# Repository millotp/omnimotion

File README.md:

# Omnimotion

A reusable three-axis motion controller — one board and one firmware stack —
shared across a family of home projects instead of building a bespoke controller
for each one.

<sub>Rev A.1, 98 × 99 mm, four layers. Rendered from the KiCad file with
[`render_pcb.py`](hardware/scripts/render_pcb.py); a few 3D models are stand-ins,
so connector shapes are approximate. A [top view](hardware/generated/omnimotion_pcb_top.jpg)
is alongside it.</sub>

## Why

A self-playing chessboard, a zen garden and a line-art drawing machine look
nothing alike, but underneath they all want the same thing: a few stepper axes
that move accurately, know where they are, and stop when something is wrong.
Rebuilding that from scratch every time buried the interesting part of each
project under motor drivers and homing routines.

Omnimotion is that common denominator, factored out once. Standing up a new
machine should be a matter of describing its geometry, not porting a driver.

## The two halves

| Folder | What it is |
| --- | --- |
| [`hardware/`](hardware/README.md) | The board — schematic, bill of materials, and the engineering rationale behind them. Both deliverables are generated from a script, so the drawing and the parts list cannot drift apart. |
| [`software/`](software/README.md) | The firmware — motion planning, step generation, stepper-driver control, homing, fault handling, and the board API that ties them together. |

Each folder has its own README with the specifics; this page is only the map.

Concretely, the board is an ESP32-S3 driving three TMC2209 stepper drivers, with
endstops, a two-pole emergency stop, a pair of switched outputs and a small
amount of general-purpose I/O. The firmware gives you one entry point that brings
that board up, works out what is actually fitted, and hands back something you
can command.

## What it optimises for

In priority order, because these trade against each other.

1. **Fail in the safe direction.** The motor drivers stay disabled unless
   firmware and the emergency-stop loop both agree they should be on, and that
   agreement is wired in copper rather than decided in software.
2. **Buildable by one person.** Every part is hand-solderable and orderable from
   a single distributor, and the parts list is short enough to read in full.
3. **Testable without hardware.** The motion logic is kept separate from
   anything chip-specific, so it can be unit-tested on a laptop.
4. **Modular.** Drivers, sensors and displays are all optional. The firmware
   surveys what is present at startup instead of assuming a fixed machine.

## Status

The schematic, bill of materials and PCB layout are complete and consistent with
each other, and the board is fully routed. The firmware builds with runnable
examples, and the motion core is covered by host tests. But **no board has been
fabricated yet**, so none of this has been validated against copper or a running
motor. Expect Rev A.1 to need a respin.

## Scope

This is hobby equipment. The emergency stop cuts motor torque in hardware, which
is a real and deliberate design choice — but it is not a certified safety
function, it does not de-energise the output rail, and it does not brake a loaded
axis. Anything that can injure someone or destroy itself needs protection that
does not depend on this board. Both folder READMEs are explicit about where the
limits sit.

## License

The firmware in `software/` is dual-licensed under either of
[Apache License 2.0](LICENSE-APACHE) or [MIT](LICENSE-MIT), at your option.

The hardware design in `hardware/` (schematic, PCB, bill of materials and the
scripts that generate them) is licensed under the
[CERN Open Hardware Licence Version 2 – Permissive](hardware/LICENSE)
(CERN-OHL-P-2.0).

Both are provided as is, with no warranty. Building and running a board that
switches motor power is entirely at your own risk.

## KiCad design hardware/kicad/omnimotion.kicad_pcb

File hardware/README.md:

# Omnimotion hardware

Rev A.1 of the Omnimotion board: a three-axis stepper motion controller built
around an ESP32-S3 module and three TMC2209 drivers.

One board is meant to serve every project in the family, so the I/O is
deliberately generic rather than tuned to any single machine — three axes, six
endstops, two switched output channels, an analogue input, and a pair of I²C
headers for whatever a given build needs.

Simplicity is a hard design constraint here rather than an afterthought: five
IC part numbers, one FET part number, one Schottky part number, and nothing on the board
that one person cannot hand-solder and reason about without a block diagram.
[`DESIGN_NOTES.md`](DESIGN_NOTES.md) keeps the honest accounting of what that
constraint costs.

## Specifications

| | |
| --- | --- |
| MCU | ESP32-S3-WROOM-1-N16R8 — dual core, 16 MB flash, 8 MB octal PSRAM, Wi-Fi/BLE, native USB |
| Axes | 3 × TMC2209-LA-T on a shared single-wire UART bus, with StallGuard4 for sensorless homing |
| Motor current | ≤ 1.4 A RMS per axis continuous, set in firmware over UART, on 0.11 Ω 2512 shunts |
| Input | 12–24 V DC via barrel jack or screw terminal, behind a 6.3 A replaceable fuse and a TVS clamp |
| 5 V rail | 3 A buck off the motor rail, multiplexed against USB with the buck as priority; 2.5 A usable |
| 3.3 V rail | Linear regulator, ~0.5 A usable |
| Endstops | 6 direct-GPIO inputs, dry contact or 3.3 V hall sensor, with polarity and role set per connector |
| Emergency stop | 2-pole normally-closed: one pole reports to firmware, the other sits in the driver-enable return |
| Outputs | 2 discrete low-side switches, 1 A each — one on 5 V, one on the 12–24 V rail |
| Other I/O | Analogue input, I²C OLED header, I²C expansion header, addressable RGB pixel, aux power take-off |
| PCB | 4 layers, 1.6 mm FR-4, ENIG |
| Assembly | 0603 minimum, 48 BOM lines covering 174 placed parts and 15 bare test pads, sized for one stencil and a hot plate |

Fifteen test points cover every rail and every bus worth scoping. Two GPIOs are
spare, and both are strapping pins, so in practice the module is full.

## Connectors

| Ref | Part / pitch | Function |
| --- | --- | --- |
| J1 | DC-005 barrel, 5.5/2.1 mm | 12–24 V DC input |
| J2 | 2-pin screw, 2.54 mm | 12–24 V DC input, high current |
| J3 | 4-pin screw, 2.54 mm | 2-pole NC emergency stop: sense + enable return |
| J4 | USB-C 2.0 | USB data and 5 V |
| J5 | 4-pin header, 2.54 mm | Console / spare UART |
| J6 | 4-pin header, 2.54 mm | I²C OLED |
| J7 | 4-pin header, 2.54 mm | I²C expansion |
| J8–J10 | 4-pin header, 2.54 mm | Stepper motors M0–M2 |
| J11–J16 | 3-pin header, 2.54 mm | Endstops, min and max per axis |
| J17 | 3-pin header, 2.54 mm | Analogue input |
| J18 | 2-pin screw, 2.54 mm | OUT1, 5 V low-side |
| J19 | 2-pin screw, 2.54 mm | OUT2, 12–24 V low-side |
| J20 | 3-pin screw, 2.54 mm | Addressable RGB strip |
| J21 | 4-pin screw, 2.54 mm | Aux power take-off |
| SW1 / SW2 | 3 × 6 mm tactile | Reset, and the boot strap for flashing |

## What is in this folder

| Path | Contents |
| --- | --- |
| `generated/omnimotion_schematic.svg` | The schematic, 9 sheets |
| `generated/omnimotion_pcb_{top,angle}.jpg` | 3D renders of the PCB, made by `scripts/render_pcb.py` |
| `generated/omnimotion_BOM.csv` | Bill of materials as one table: a row per part, with manufacturer and Digi-Key part numbers, the KiCad footprint it needs, the sheets it appears on, and the datasheet rating that justifies it |
| `generated/omnimotion_footprints.html` | Printable parts list plus every distinct footprint the BOM needs drawn at 1:1, to lay the real parts on before the PCB is ordered. The generator also writes a PDF of it when Chrome is installed; that copy is not committed |
| `scripts/gen_schematic.py` | Generator for the schematic, and the source of truth for the design |
| `scripts/gen_bom.py` | Harvests the BOM out of the generator |
| `scripts/gen_footprint_sheet.py` | Builds the footprint sheet from the BOM and the footprints placed on the KiCad PCB |
| `scripts/render_pcb.py` | Renders the KiCad PCB to JPEG, or exports it as a STEP and GLB 3D model to paths you give, through Docker, no local KiCad needed |
| `scripts/check_kicad.py` | Compares the KiCad schematic with the generator, net by net, and the KiCad PCB with that schematic |
| `scripts/kicadlib.py` | Read-only KiCad file parsing (s-expressions, schematic connectivity, PCB pads) shared by the two scripts above |
| `scripts/schlib.py` | Minimal SVG primitive and symbol library the generator draws with |
| `DESIGN_NOTES.md` | Design rationale, datasheet verification, layout constraints, known risks |
| `kicad/` | KiCad 10 project `omnimotion`: the schematic, and the routed 4-layer PCB, 98 × 99 mm. Both follow the generated design and are checked against it by `check_kicad.py` |
| `LICENSE` | CERN-OHL-P-2.0, covering everything in this folder |

The sheets are ordered so you can read them front to back: 1 is the architecture
and power tree, 2 and 3 are input protection and the supplies, 4 is the MCU, 5–7
are one axis each, 8 is the endstops and the I²C headers, and 9 is the outputs,
test points and bring-up order. `DESIGN_NOTES.md` has the full index.

## Regenerating the deliverables

```bash
cd hardware
python3 scripts/gen_schematic.py && python3 scripts/gen_bom.py
```

No dependencies beyond a Python 3 interpreter; the generator writes SVG directly.
Add `--check` to either script to regenerate in memory and fail if the committed
file is stale.

Edit the generator, never the SVG or the CSV. Both scripts refuse to run on an
ambiguous drawing: a component terminal or wire end that touches nothing, a wire
drawn through another symbol, or a T-junction without a dot. `gen_bom.py` reads
its component list back out of the schematic generator and fails loudly on a
duplicate reference designator or a value with no BOM entry, which is what keeps
the two from disagreeing.

`python3 scripts/check_kicad.py` checks the `kicad/` project against the generator
without needing KiCad installed. It reports parts that are missing or extra,
values that differ, pins on the wrong net, design nets that KiCad shorts
together, and any part, footprint or pad net where the PCB has drifted from the
KiCad schematic. It also holds every footprint to the one the BOM names. It
exits non-zero when anything differs.

`python3 scripts/gen_footprint_sheet.py` rebuilds the footprint sheet after a BOM or PCB
change. It draws the footprint each BOM line names: from the PCB's own copy
when the PCB has it, compared pad by pad with the library (the project's
`.pretty` folder or the KiCad library downloaded into
`build/footprints/`), and from the library otherwise. References that are
missing from the PCB, or that sit on another footprint there, are flagged in
red. Capacitors show their voltage and dielectric. It prints the PDF with Google
Chrome when it is installed.

## Rendering the PCB

```bash
python3 scripts/render_pcb.py images
python3 scripts/render_pcb.py models board.step board.glb
```

`images` rewrites the two `generated/omnimotion_pcb_*.jpg` images from
`kicad/omnimotion.kicad_pcb`. `models` exports the same board as a 3D model and
needs a path for both the STEP and the GLB file. It has no default location,
because the files are several megabytes and are not kept in the repository. The
models take well under a minute, the renders a couple of minutes. The only
requirement is Docker, so KiCad does not have to be installed. The script:

1. Reads the 3D model paths out of the PCB and downloads each one, once, from
   the [official KiCad 3D library](https://gitlab.com/kicad/libraries/kicad-packages3D)
   into `build/3dmodels/` (git-ignored). The `kicad/kicad` image ships without
   3D models, which is why this step exists.
2. Pulls the `kicad/kicad:10.0` image if it is missing, and runs
   `kicad-cli pcb render` in it with the model folder mounted, once each for
   a top view and an angled perspective view.
3. Exports the board as a coloured 3D model with `kicad-cli pcb export step` and
   `export glb`: the board body, the component models and the soldermask, without
   copper pads, tracks, zones or silkscreen (the pads alone are 60% of the
   triangles). The STEP (6.8 MB) keeps solids and colours for CAD; the GLB (3.7 MB,
   about 95,000 triangles) carries PBR materials for viewers. Both are far
   heavier than a real-time scene should draw, so a consumer that animates the
   board in a browser should decimate them.
4. Copies the outputs out with `docker cp`, because a bind-mounted output folder
   is not reliably writable by the container's user. Each run names its container
   after its process id, so two runs at once do not stop each other.

The image is published for amd64 only. On Apple Silicon it runs under emulation,
and the two views take about a minute and a half together; after the first run the
models and the image are cached.

Four parts have no exact model in the KiCad library. The PCB points the Kycon
barrel jack (J1), the TMC2209 VQFN-28 (U5–U7) and the LMR33630 HTSOP-8 (U1) at
the closest library models, so their 3D shapes are approximate (the QFN model has
a 3.35 mm exposed pad against the footprint's 3.7 mm). The Littelfuse Nano2 fuse
holder (F1) has no model at all and is drawn as bare pads. Adjust the angle, zoom
or size in `VIEWS` at the top of the script.

## Building one

1. **Order.** Every orderable line carries a manufacturer part number and a
   Digi-Key link, so the board goes into a single cart. The four lines that do
   not are the PCB itself, the bare test pads, the mounting hardware and the
   optional driver heatsinks.
2. **Assemble.** Nothing is smaller than 0603 and there is exactly one FET part
   number and one Schottky part number on the board. Screw terminals, the USB-C
   hold-down and the 2.54 mm headers stay through-board on purpose: a yanked
   motor or endstop cable will lift an SMD pad. The ten signal headers snap
   off a single 40-pin breakaway strip; the motor headers are unkeyed, so mark
   pin 1 and never hot-plug a motor.
3. **Bring up in the printed order.** Sheet 9 lists it step by step — rails
   before ICs, the MCU before any driver, one driver before three. TP1–TP4 are
   the rail-by-rail power check and are worth doing before an IC goes on.
4. **Before ordering the PCB**, confirm the buck inductor footprint against the
   part you actually bought, and run DRC with your fab's real constraints.

## Limits worth knowing before you build

The full list is in [`DESIGN_NOTES.md`](DESIGN_NOTES.md); these are the ones that
change what you can safely do with the board.

- **Nothing here has been fabricated.** No claim in this folder has been checked
  against a physical board.
- **No overvoltage protection on the motor rail.** This is the headline risk.
  The TVS does not contain a large enough transient before the drivers' absolute
  maximum is exceeded; regeneration can do the same. Supply choice is the
  protection: a bench supply or a good brick on a short lead, not a long
  inductive feed or a supply shared with contactors.
- **The emergency stop cuts torque, not power.** Opening it releases the drivers
  in copper with no firmware involvement, which is the point — but the motor rail
  and the 24 V output stay live, and the motors coast rather than brake. A loaded
  vertical axis will back-drive. If something must drop mechanically, use a
  3-pole button or an external contactor.
- **Reverse polarity blows the fuse** rather than being blocked. The fuse is a
  replaceable cartridge, so the cost is a fuse — but feed the board 12–24 V and
  nothing else.
- **1.4 A RMS per axis is contingent on thermals.** The driver exposed pads are
  the entire heatsink; the thermal vias and the solid inner ground plane are not
  optional, and above ~1.2 A RMS per axis you want the adhesive heatsinks listed
  at the end of the BOM.
- **USB-only power is a 500 mA budget** enforced by a thermal PTC, not a precise
  limiter. No motors, no output loads.
- **The external inputs have no clamp diodes.** A 1 kΩ series resistor and a
  100 nF cap on each endstop and on J17 cover ESD, but nothing clamps a
  sustained wrong voltage. 24 V into a SIG pin will cost you a GPIO on a
  soldered-down module.

## Going deeper

[`DESIGN_NOTES.md`](DESIGN_NOTES.md) is the engineering record: which datasheet
was consulted for what and where one changed the plan, the emergency-stop
architecture in full, the power budget rail by rail, the pin map the firmware
depends on, the part vocabulary for home assembly, KiCad stackup and routing
constraints, and the open risks.

The firmware that drives this board is in [`../software/`](../software/README.md).

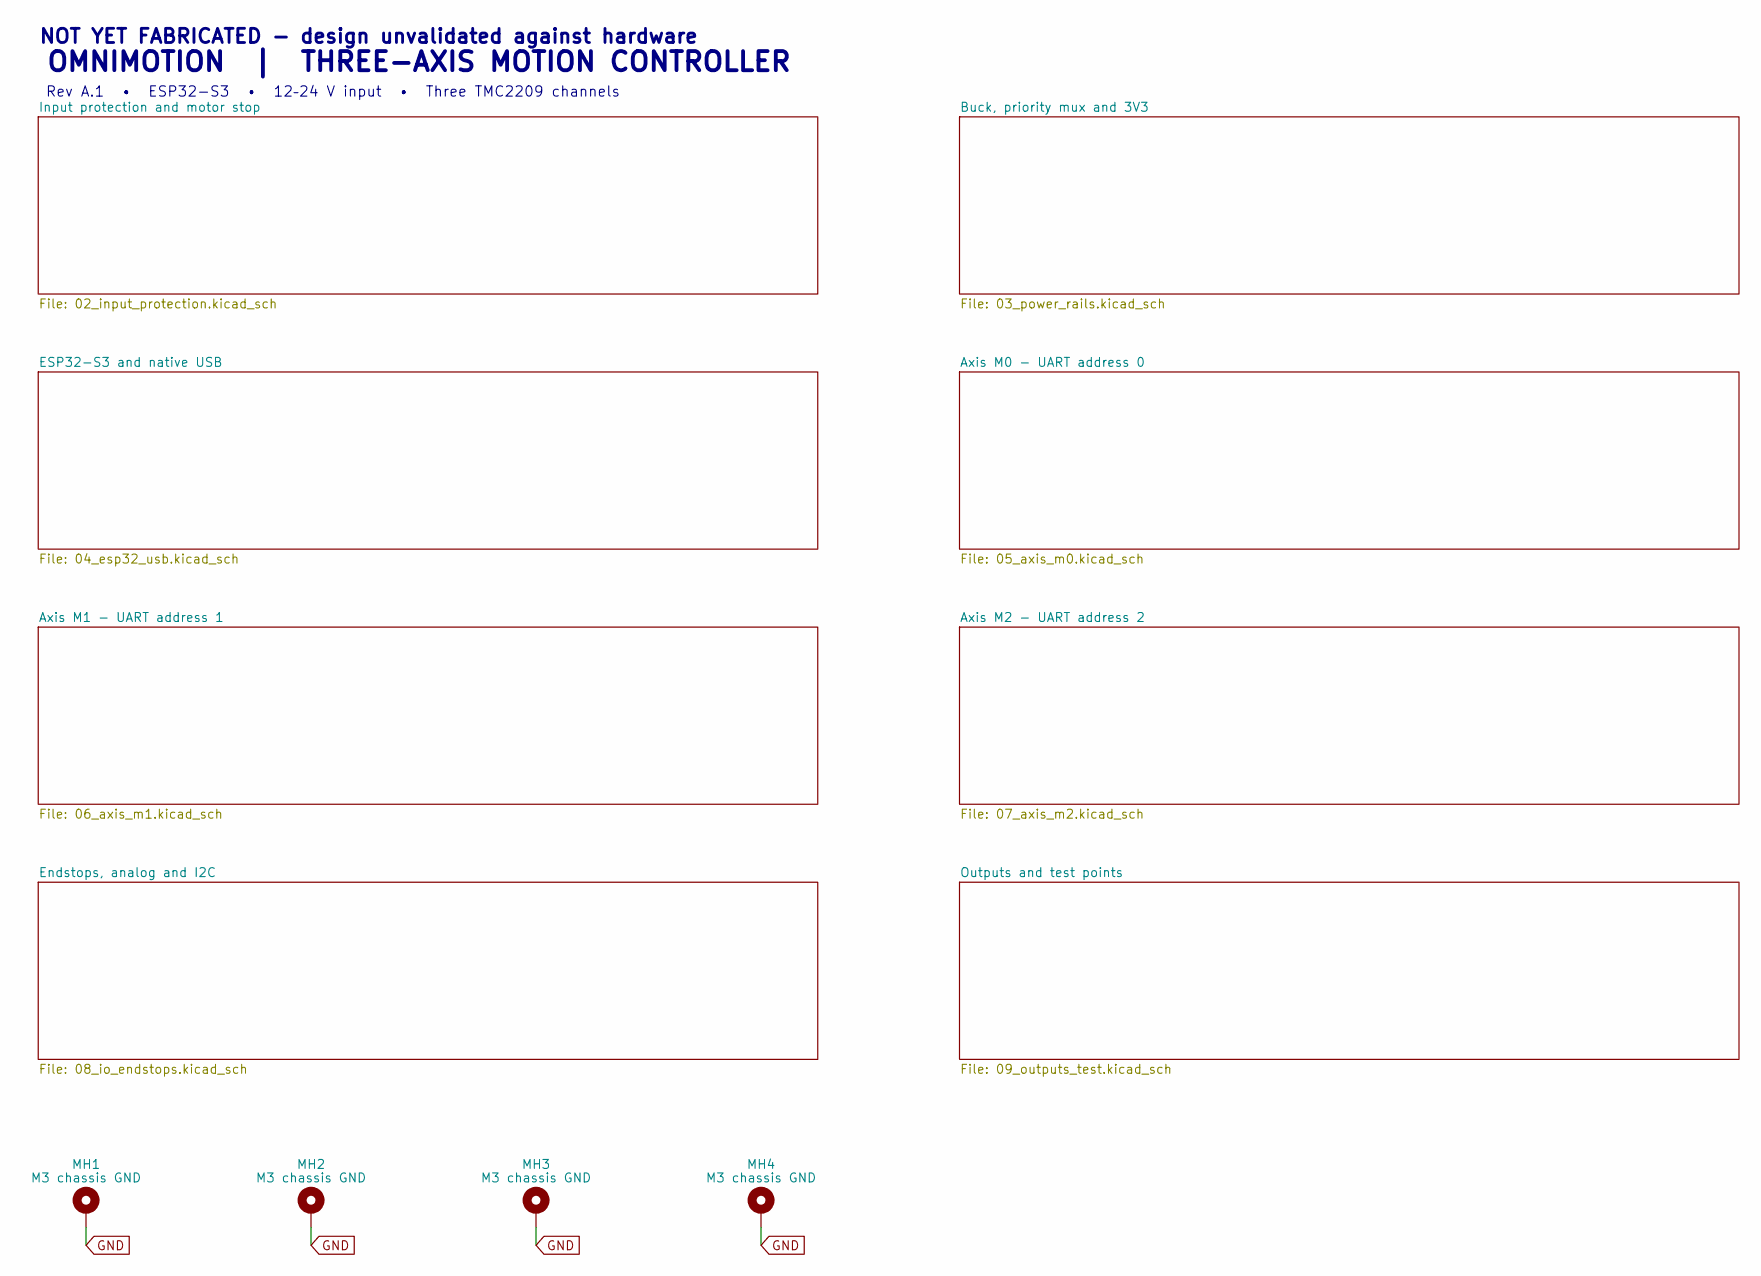
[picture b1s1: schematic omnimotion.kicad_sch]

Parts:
MH1, MH2, MH3, MH4: M3 chassis GND; MountingHole_3.2mm_M3_ISO7380_Pad

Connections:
GND: MH1.1 (1_1), MH2.1 (1_1), MH3.1 (1_1), MH4.1 (1_1); also elsewhere on the board

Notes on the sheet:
NOT YET FABRICATED - design unvalidated against hardware
OMNIMOTION | THREE-AXIS MOTION CONTROLLER
Rev A.1 • ESP32-S3 • 12–24 V input • Three TMC2209 channels

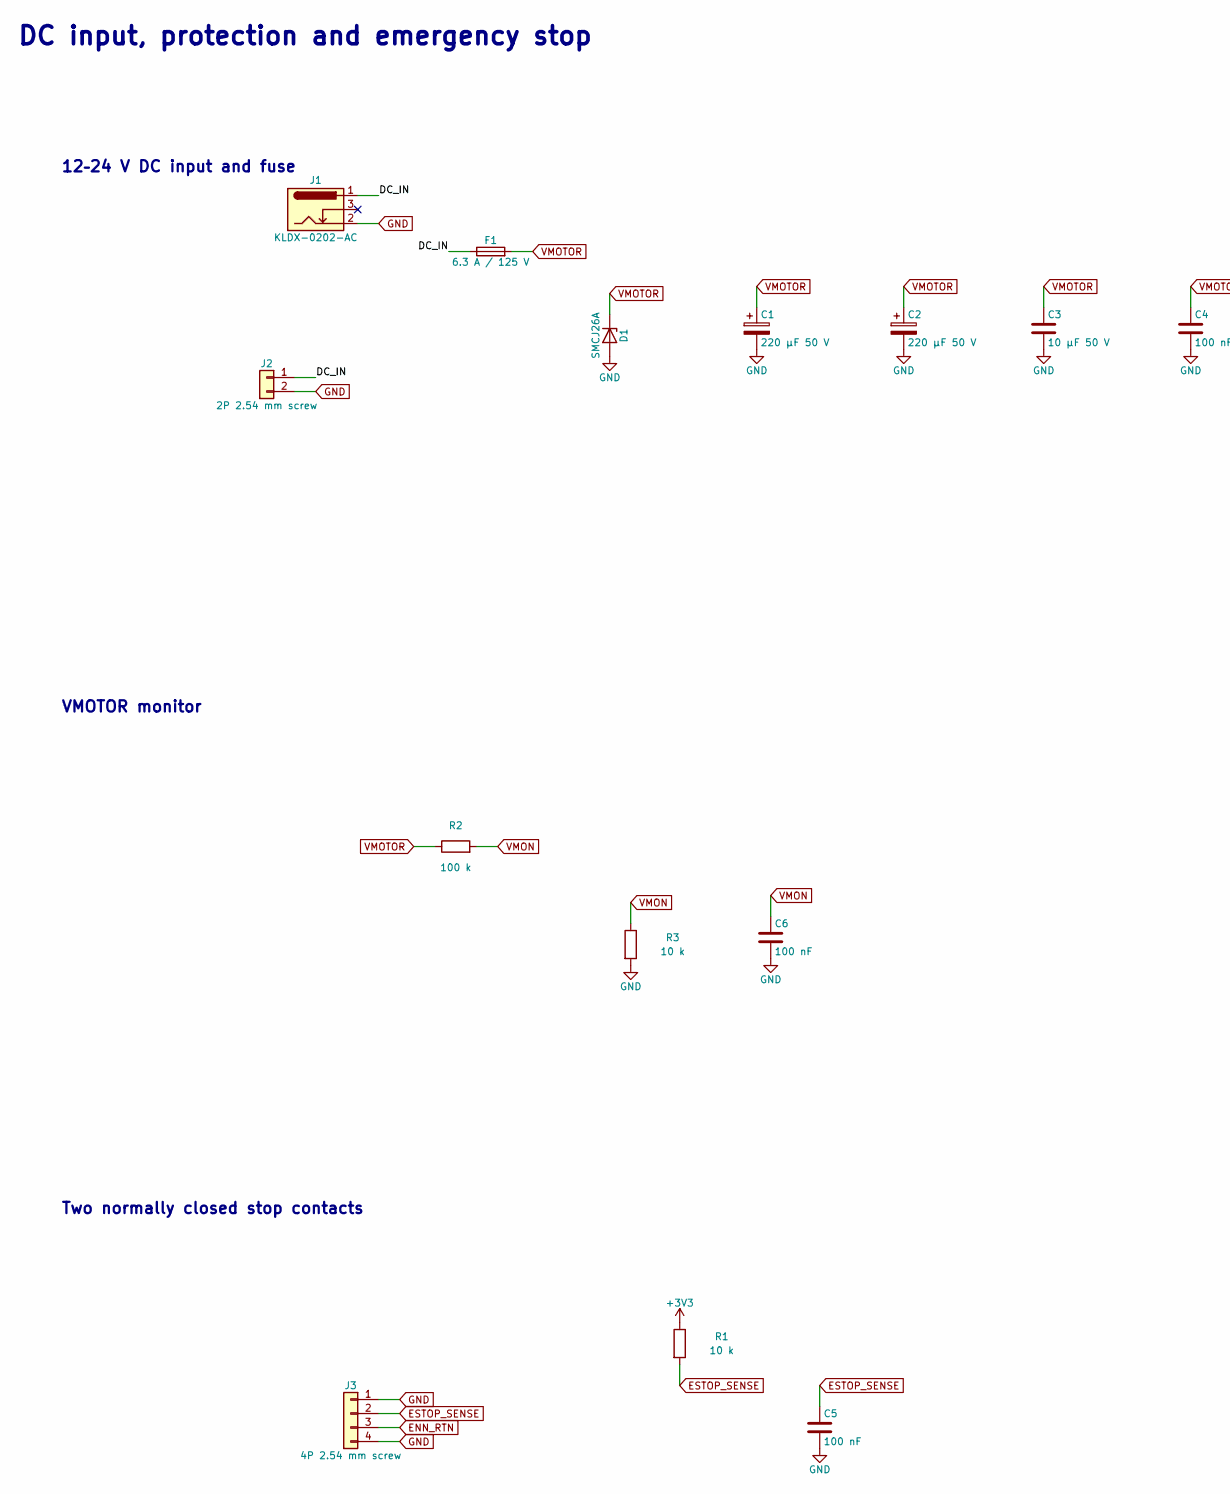
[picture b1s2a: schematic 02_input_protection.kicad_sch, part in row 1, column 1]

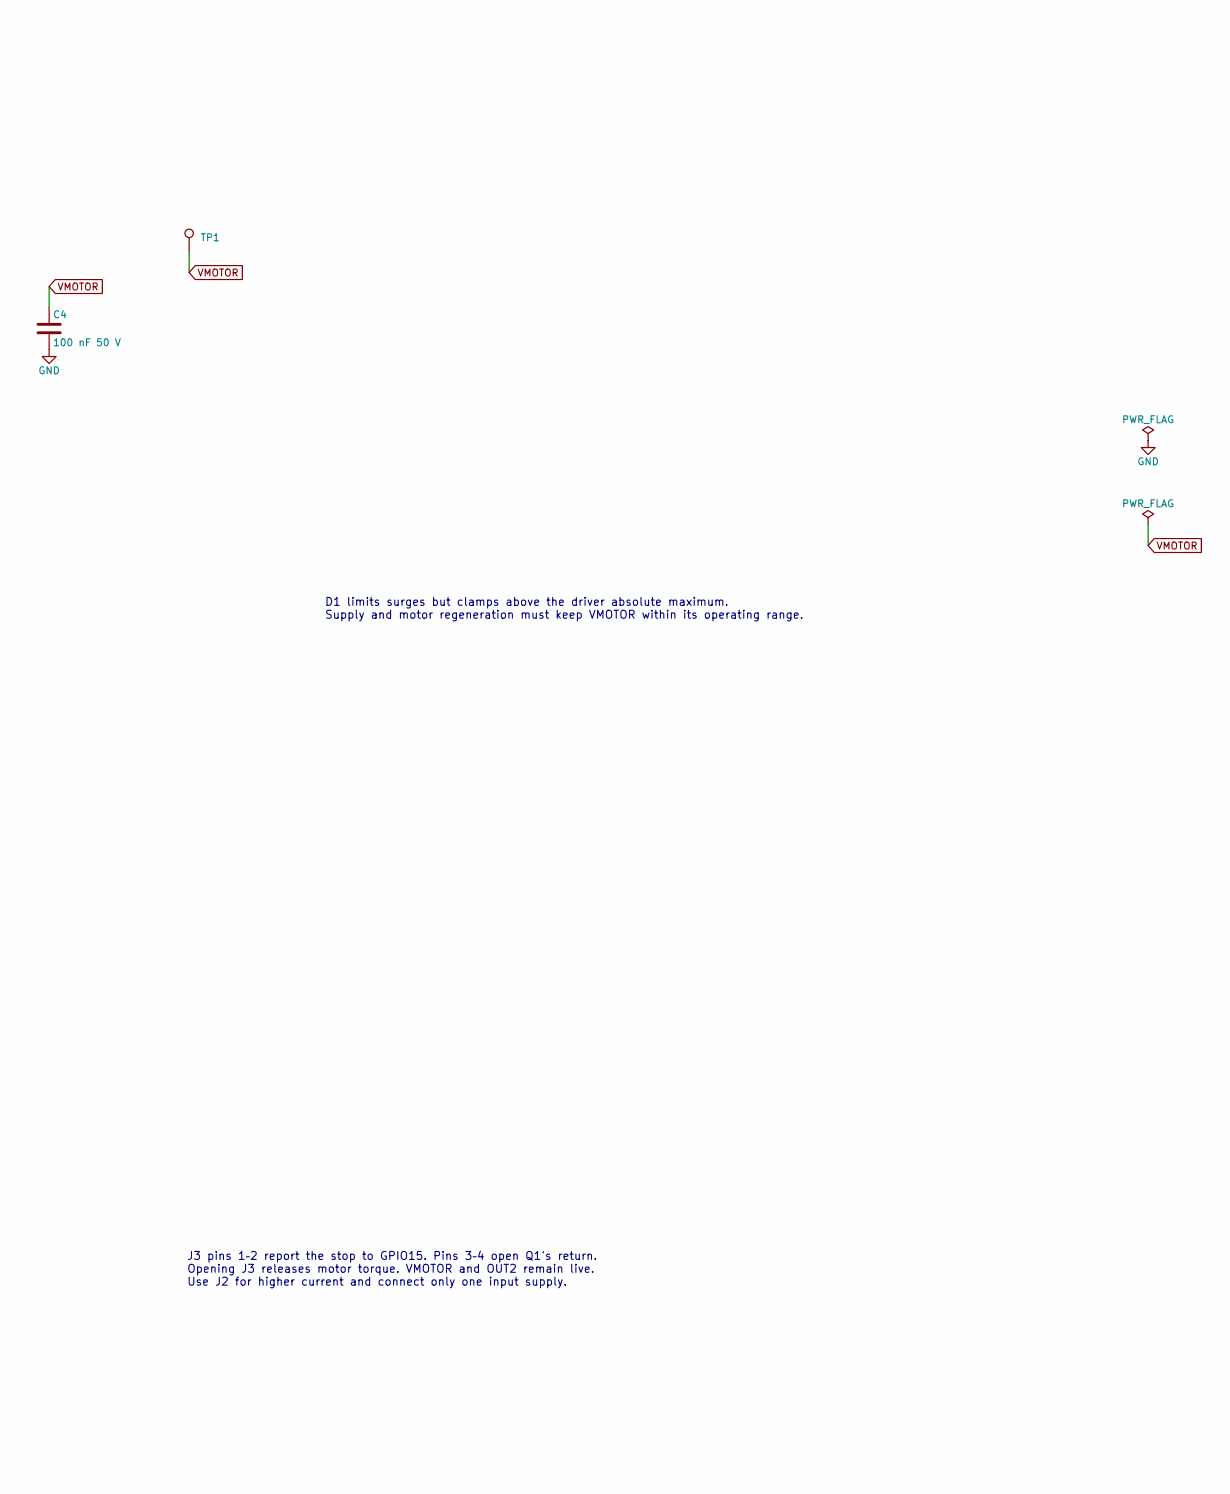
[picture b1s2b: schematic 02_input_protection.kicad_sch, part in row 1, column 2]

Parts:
C1, C2: 220 µF 50 V; CP_Elec_10x10.5
C3: 10 µF 50 V; C_1210_3225Metric
C4: 100 nF 50 V; C_0603_1608Metric
C5, C6: 100 nF; C_0603_1608Metric
D1: SMCJ26A; D_SMC
F1: 6.3 A / 125 V; Fuseholder_Littelfuse_Nano2_154x
J1: KLDX-0202-AC; BarrelJack_Kycon_KLDX-0202-xC_Horizontal
J2: 2P 2.54 mm screw; TerminalBlock_Phoenix_MPT-0,5-2-2.54_1x02_P2.54mm_Horizontal
J3: 4P 2.54 mm screw; TerminalBlock_Phoenix_MPT-0,5-4-2.54_1x04_P2.54mm_Horizontal
R1, R3: 10 k; R_0603_1608Metric
R2: 100 k; R_0603_1608Metric
TP1: Test point; TestPoint_Pad_D1.0mm

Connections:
+3V3: R1.1; also elsewhere on the board
/Input protection and motor stop/DC_IN: F1.1, J1.1, J2.1
ENN_RTN: J3.3; also elsewhere on the board
ESTOP_SENSE: C5.1, J3.2, R1.2; also elsewhere on the board
GND: C1.2, C2.2, C3.2, C4.2, C5.2, C6.2, D1.2 (A), J1.2, J2.2, J3.1, J3.4, R3.2; also elsewhere on the board
VMON: C6.1, R2.2, R3.1; also elsewhere on the board
VMOTOR: C1.1, C2.1, C3.1, C4.1, D1.1 (K), F1.2, R2.1, TP1.1 (1_1); also elsewhere on the board

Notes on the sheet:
DC input, protection and emergency stop
12–24 V DC input and fuse
VMOTOR monitor
Two normally closed stop contacts
J3 pins 1–2 report the stop to GPIO15. Pins 3–4 open Q1’s return. Opening J3 releases motor torque. VMOTOR and OUT2 remain live. Use J2 for higher current and connect only one input supply.
D1 limits surges but clamps above the driver absolute maximum. Supply and motor regeneration must keep VMOTOR within its operating range.

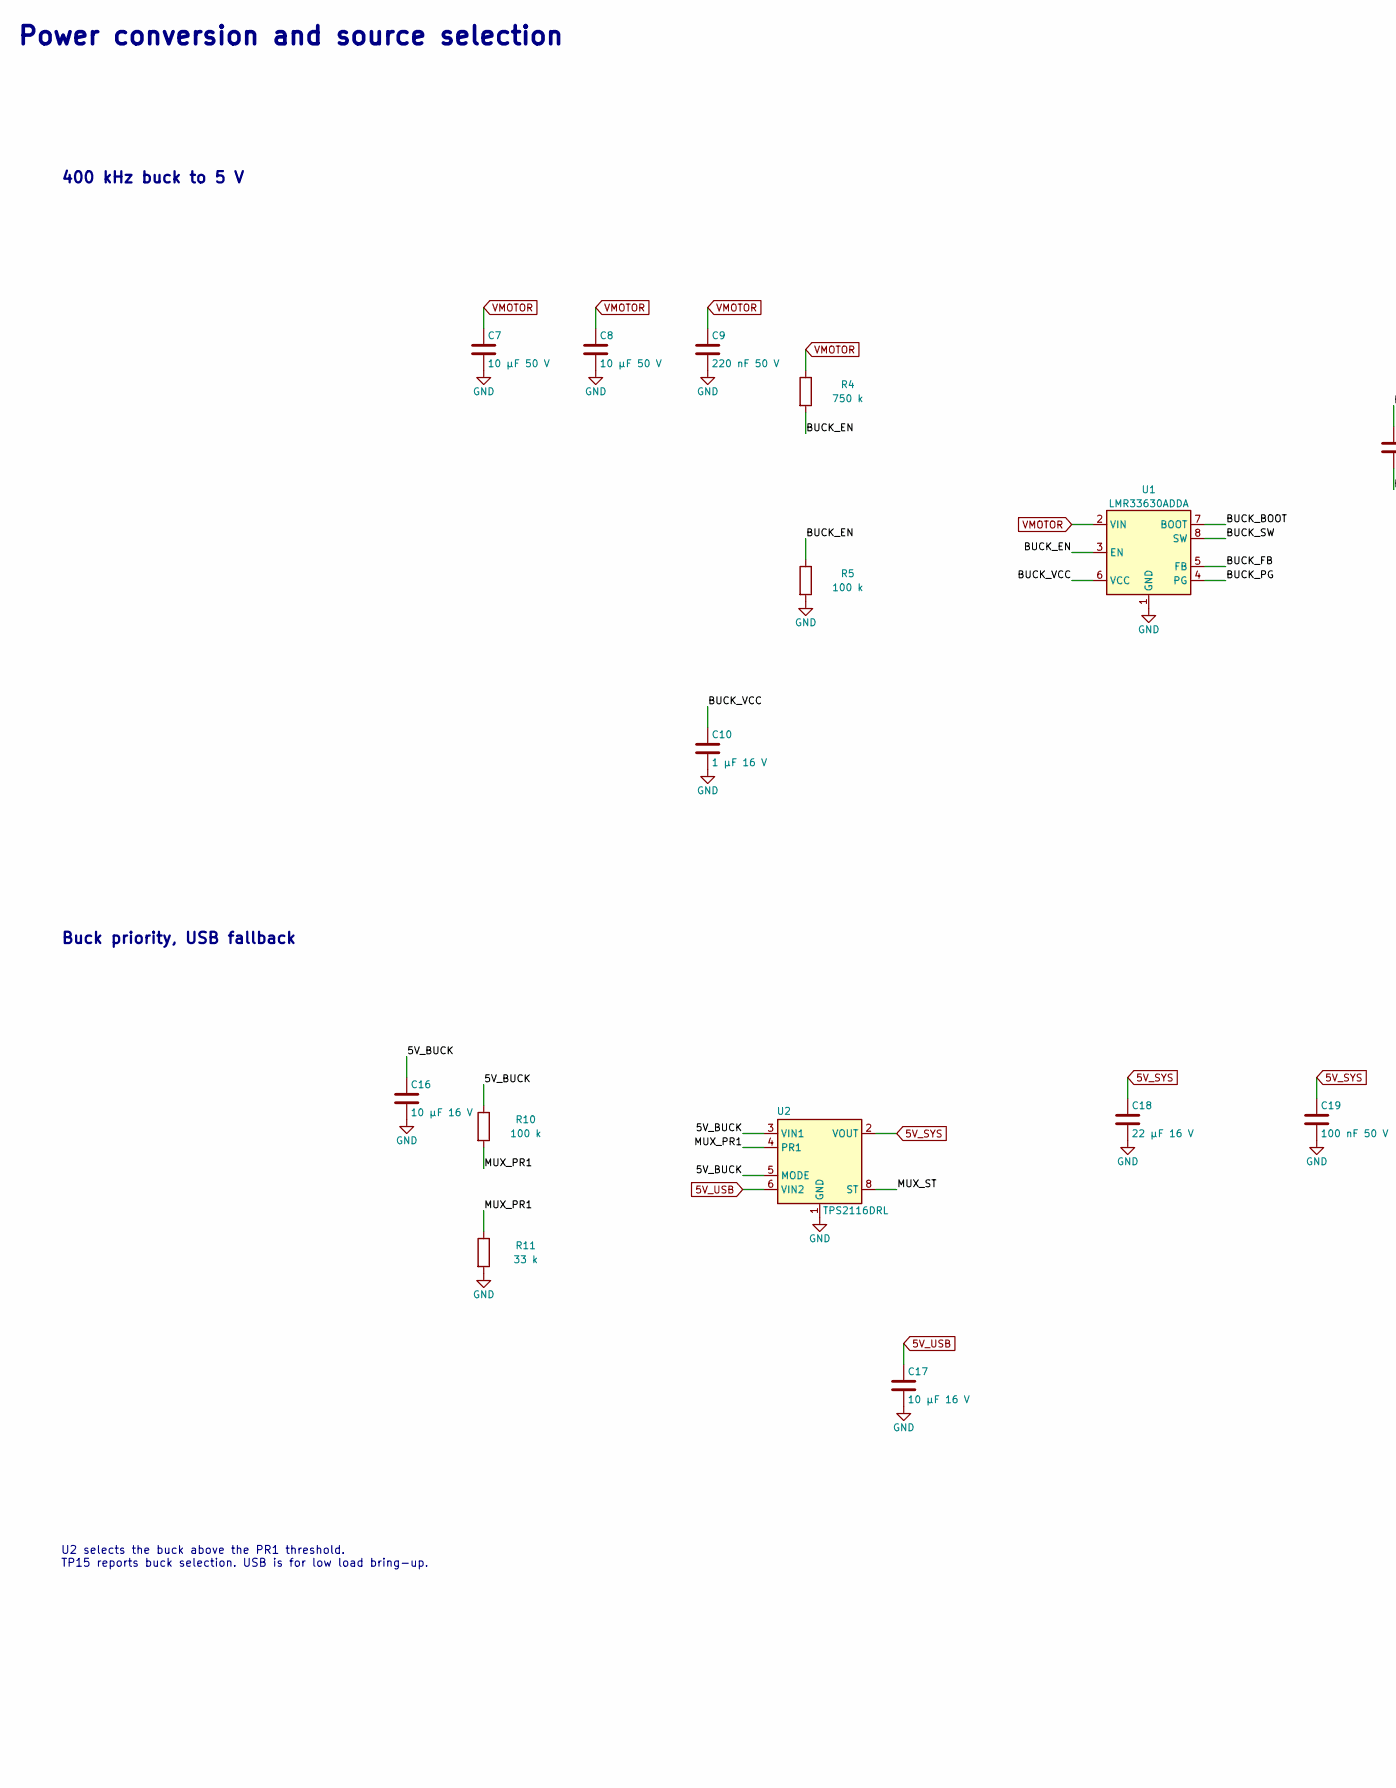
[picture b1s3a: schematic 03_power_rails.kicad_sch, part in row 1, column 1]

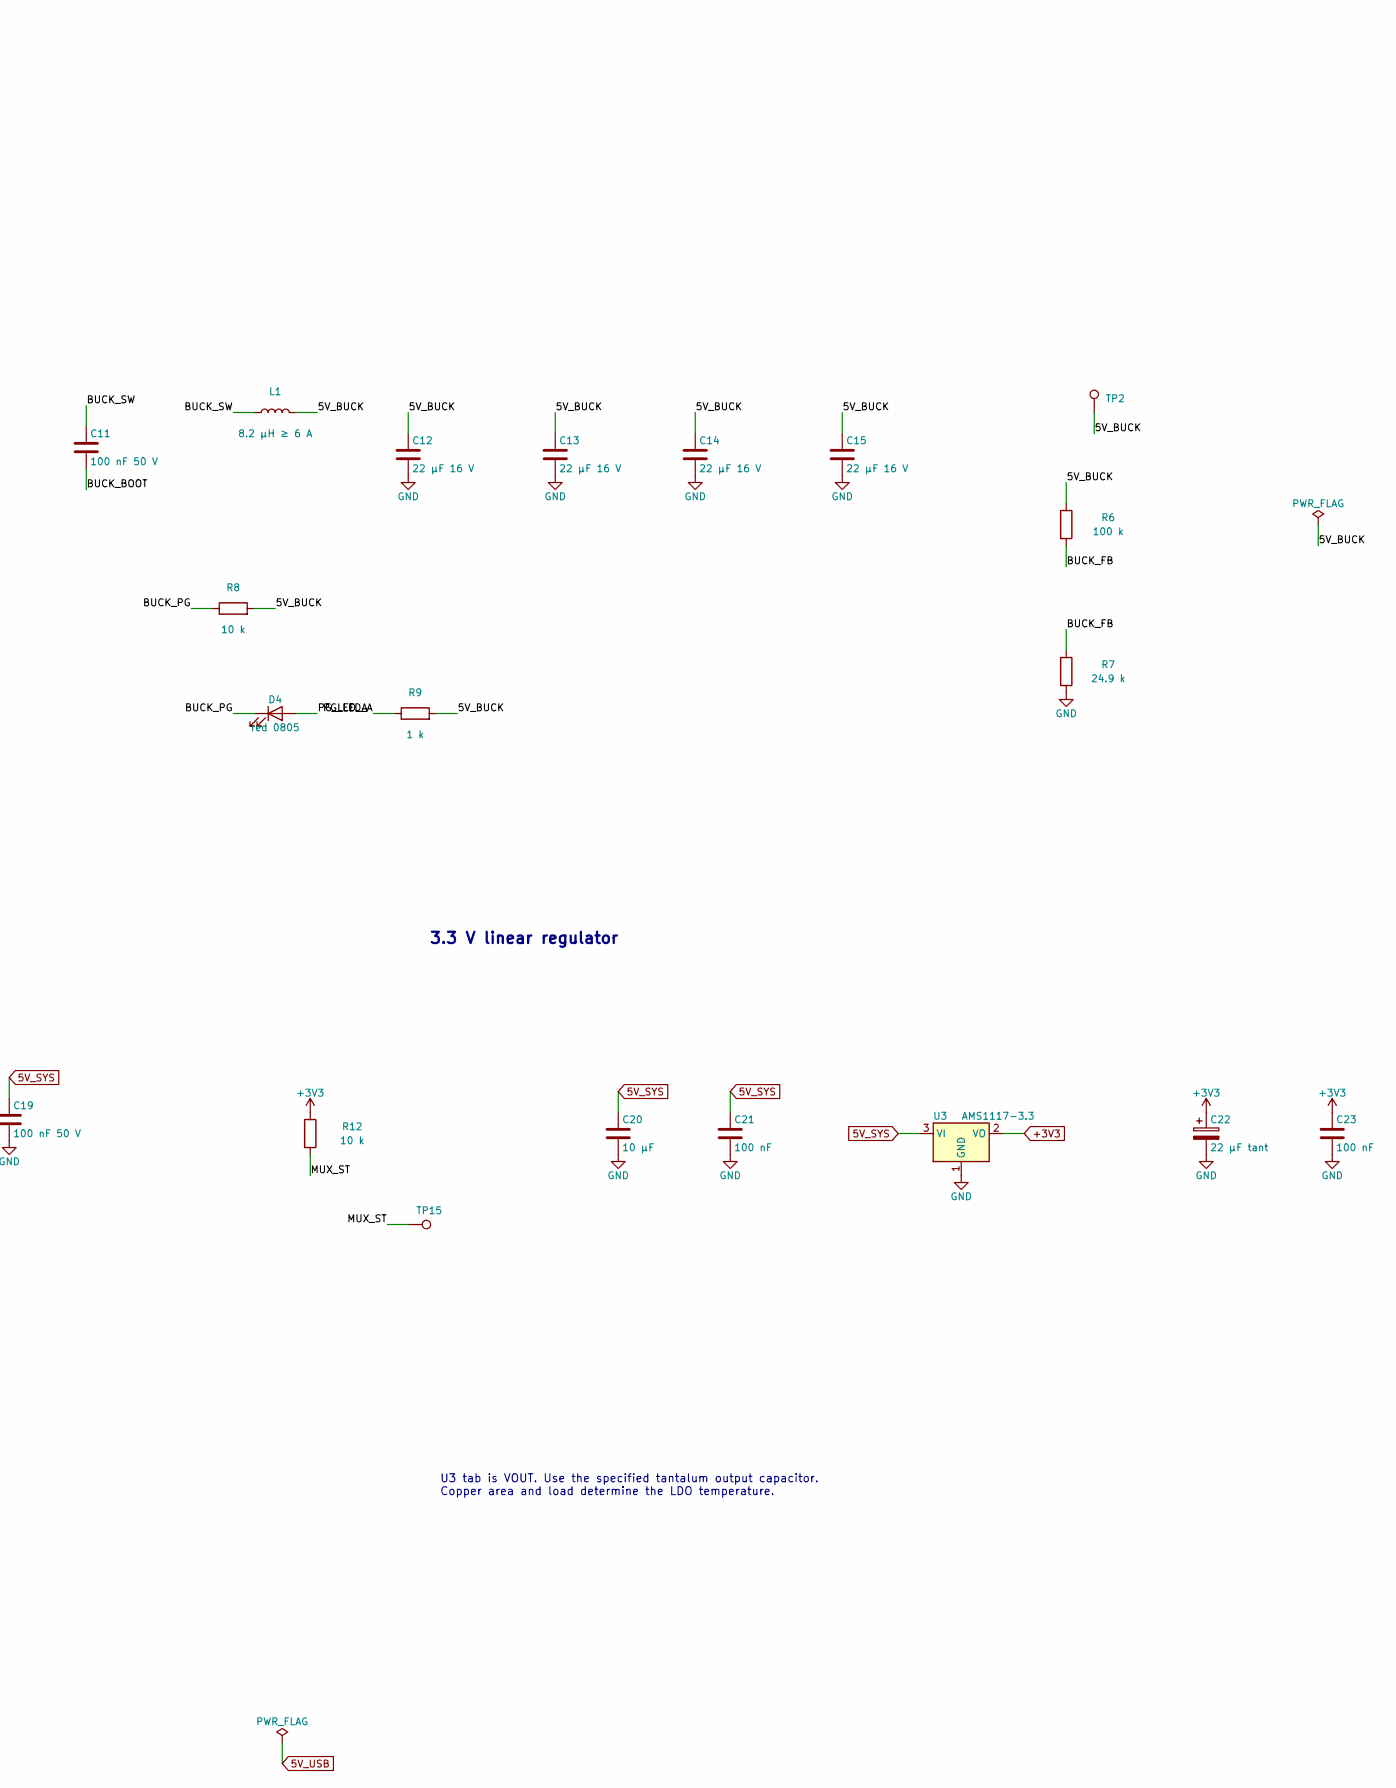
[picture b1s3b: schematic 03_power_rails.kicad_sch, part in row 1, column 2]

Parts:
C7, C8: 10 µF 50 V; C_1210_3225Metric
C9: 220 nF 50 V; C_0603_1608Metric
C10: 1 µF 16 V; C_0603_1608Metric
C11, C19: 100 nF 50 V; C_0603_1608Metric
C12, C13, C14, C15, C18: 22 µF 16 V; C_1206_3216Metric
C16, C17: 10 µF 16 V; C_0805_2012Metric
C20: 10 µF; C_0805_2012Metric
C21, C23: 100 nF; C_0603_1608Metric
C22: 22 µF tant; CP_EIA-3528-21_Kemet-B
D4: red 0805; LED_0805_2012Metric
L1: 8.2 µH ≥ 6 A; L_Bourns_SRP1265A
R4: 750 k; R_0603_1608Metric
R5, R6, R10: 100 k; R_0603_1608Metric
R7: 24.9 k; R_0603_1608Metric
R8, R12: 10 k; R_0603_1608Metric
R9: 1 k; R_0603_1608Metric
R11: 33 k; R_0603_1608Metric
TP2, TP15: Test point; TestPoint_Pad_D1.0mm
U1: LMR33630ADDA; LMR33630_HSOP8_ThermalVias_9
U2: TPS2116DRL; SOT-583-8
U3: AMS1117-3.3; SOT-223-3_TabPin2

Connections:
5V_SYS: C18.1, C19.1, C20.1, C21.1, U2.2 (VOUT), U2.7 (VOUT), U3.3 (VI); also elsewhere on the board
5V_USB: C17.1, U2.6 (VIN2); also elsewhere on the board
+3V3: C22.1, C23.1, R12.1, U3.2 (VO); also elsewhere on the board
/Buck, priority mux and 3V3/5V_BUCK: C12.1, C13.1, C14.1, C15.1, C16.1, L1.2, R6.1, R8.2, R9.2, R10.1, TP2.1 (1_1), U2.3 (VIN1), U2.5 (MODE)
/Buck, priority mux and 3V3/BUCK_BOOT: C11.2, U1.7 (BOOT)
/Buck, priority mux and 3V3/BUCK_EN: R4.2, R5.1, U1.3 (EN)
/Buck, priority mux and 3V3/BUCK_FB: R6.2, R7.1, U1.5 (FB)
/Buck, priority mux and 3V3/BUCK_PG: D4.1 (K), R8.1, U1.4 (PG)
/Buck, priority mux and 3V3/BUCK_SW: C11.1, L1.1, U1.8 (SW)
/Buck, priority mux and 3V3/BUCK_VCC: C10.1, U1.6 (VCC)
/Buck, priority mux and 3V3/MUX_PR1: R10.2, R11.1, U2.4 (PR1)
/Buck, priority mux and 3V3/MUX_ST: R12.2, TP15.1 (1_1), U2.8 (ST)
/Buck, priority mux and 3V3/PG_LED_A: D4.2 (A), R9.1
GND: C7.2, C8.2, C9.2, C10.2, C12.2, C13.2, C14.2, C15.2, C16.2, C17.2, C18.2, C19.2, C20.2, C21.2, C22.2, C23.2, R5.2, R7.2, R11.2, U1.1 (GND), U1.9 (GND), U2.1 (GND), U3.1 (GND); also elsewhere on the board
VMOTOR: C7.1, C8.1, C9.1, R4.1, U1.2 (VIN); also elsewhere on the board

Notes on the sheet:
400 kHz buck to 5 V
3.3 V linear regulator
U2 selects the buck above the PR1 threshold. TP15 reports buck selection. USB is for low load bring-up.
Buck priority, USB fallback
U3 tab is VOUT. Use the specified tantalum output capacitor. Copper area and load determine the LDO temperature.
Power conversion and source selection
